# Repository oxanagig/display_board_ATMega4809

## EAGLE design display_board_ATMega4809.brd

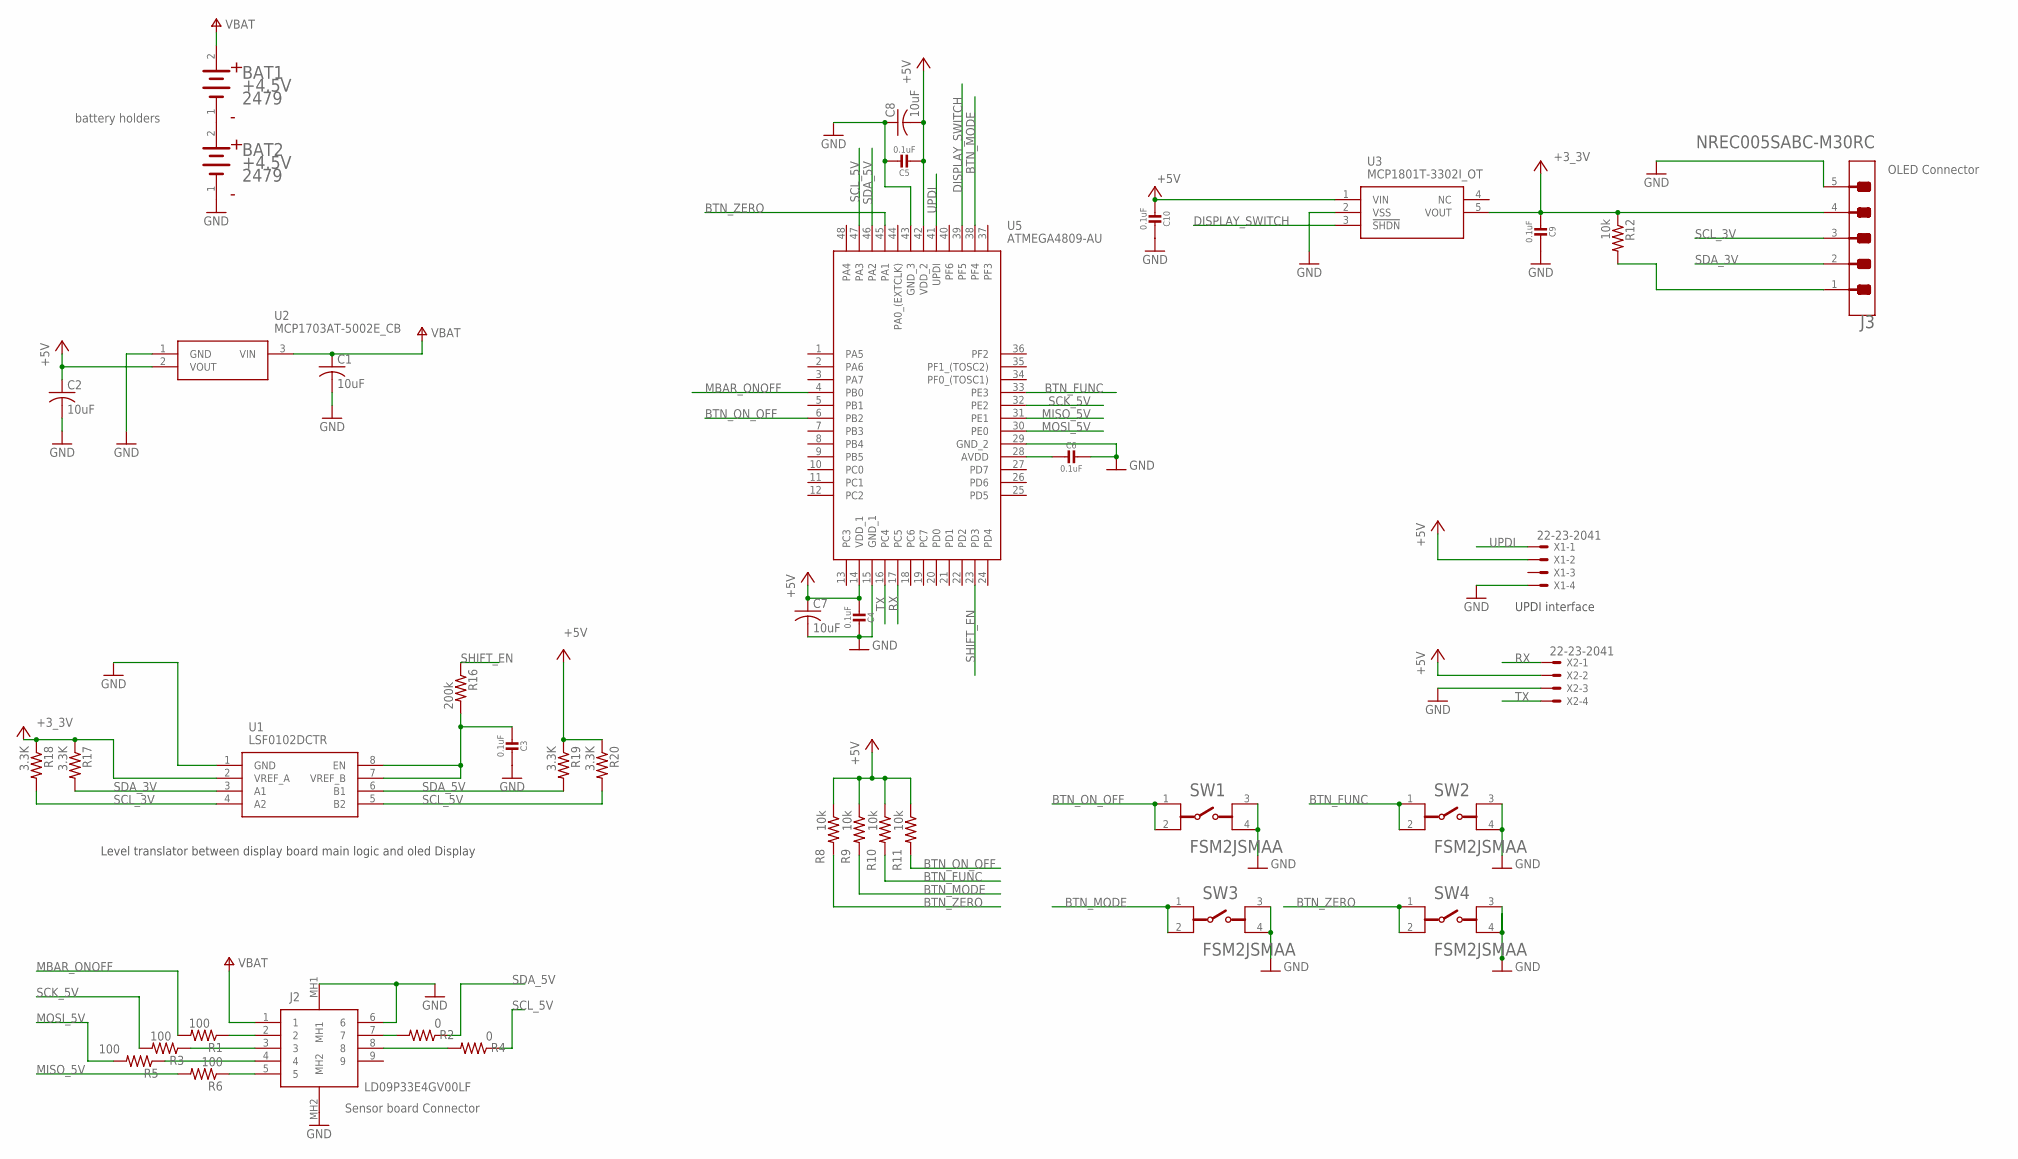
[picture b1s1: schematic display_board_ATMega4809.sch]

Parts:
BAT1, BAT2: KEYSTONE_2479KEYSTONE_2479_0_0; KEYSTONE_2479_0
C1, C2, C7, C8: 10uF; C0805
C3, C4, C5, C6, C9, C10: 0.1uF; _0603MP
J2: LD09P33E4GV00LF
J3: SULLINS_NREC005SABC-M30RCSULLINS_NREC005SABC-M30R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; SULLINS_NREC005SABC-M30RC_0
R1, R3, R5, R6: 100; R0603
R2, R4: 0; R0603
R8, R9, R10, R11, R12: 10k; R0603
R16: 200k; R0603
R17, R18, R19, R20: 3.3K; R0603
SW1, SW2, SW3, SW4: TE_CONNECTIVITY_FSM2JSMAATE_CONNECTIVITY_FSM2JSMA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; TE_CONNECTIVITY_FSM2JSMAA_0
U1: LSF0102DCTR; SOP65P400X130-8N
U2: MCP1703AT-5002E_CB; SOT95P255X145-3N
U3: MCP1801T-3302I_OT; SOT95P270X145-5N
U5: ATMEGA4809-AU; QFP50P900X900X120-48N
X1, X2: 22-23-2041

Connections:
+3V3: C9.2, J3.4, R12.1, R17.1, R18.1, U1.2 (VREF_A), U3.5 (VOUT)
+5V: C2.1, C4.2, C5.2, C7.1, C8.2, C10.2, R8.1, R9.1, R10.1, R11.1, R19.1, R20.1, U2.2 (VOUT), U3.1 (VIN), U5.14 (VDD_1), U5.42 (VDD_2), X1.2, X2.2
BTN_FUNC: R10.2, SW2.1, SW2.2, U5.33 (PE3)
BTN_MODE: R9.2, SW3.1, SW3.2, U5.38 (PF4)
BTN_ON_OFF: R11.2, SW1.1, SW1.2, U5.6 (PB2)
BTN_ZERO: R8.2, SW4.1, SW4.2, U5.45 (PA1)
DISPLAY_RESET: J3.1, R12.2
DISPLAY_SWITCH: U3.3 (!SHDN), U5.39 (PF5)
GND: BAT2.1 (CATHODE), C1.2, C2.2, C3.1, C4.1, C5.1, C6.1, C7.2, C8.1, C9.1, C10.1, J2.6, J2.MH1, J2.MH2, J3.5, SW1.3, SW1.4, SW2.3, SW2.4, SW3.3, SW3.4, SW4.3, SW4.4, U1.1 (GND), U2.1 (GND), U3.2 (VSS), U5.15 (GND_1), U5.29 (GND_2), U5.43 (GND_3), X1.4, X2.3
MBAR_ONOFF: R1.2, U5.4 (PB0)
MISO_5V: R6.2, U5.31 (PE1)
MOSI_5V: R5.2, U5.30 (PE0)
unnamed: C3.2, R16.2, U1.7 (VREF_B), U1.8 (EN)
unnamed: J2.2, R1.1
unnamed: J2.3, R3.1
unnamed: J2.7, R2.2
unnamed: J2.4, R5.1
unnamed: J2.5, R6.1
unnamed: C6.2, U5.28 (AVDD)
unnamed: J2.8, R4.2
unnamed: BAT1.1 (CATHODE), BAT2.2 (ANODE)
RX: U5.17 (PC5), X2.1
SCK_5V: R3.2, U5.32 (PE2)
SCL_3V: J3.3, R18.2, U1.4 (A2)
SCL_5V: R4.1, R20.2, U1.5 (B2), U5.47 (PA3)
SDA_3V: J3.2, R17.2, U1.3 (A1)
SDA_5V: R2.1, R19.2, U1.6 (B1), U5.46 (PA2)
SHIFT_EN: R16.1, U5.23 (PD3)
TX: U5.16 (PC4), X2.4
UPDI: U5.41 (UPDI), X1.1
VBAT: BAT1.2 (ANODE), C1.1, J2.1, U2.3 (VIN)

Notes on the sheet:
OLED Connector
Sensor board Connector
battery holders
UPDI interface
Level translator between display board main logic and oled Display

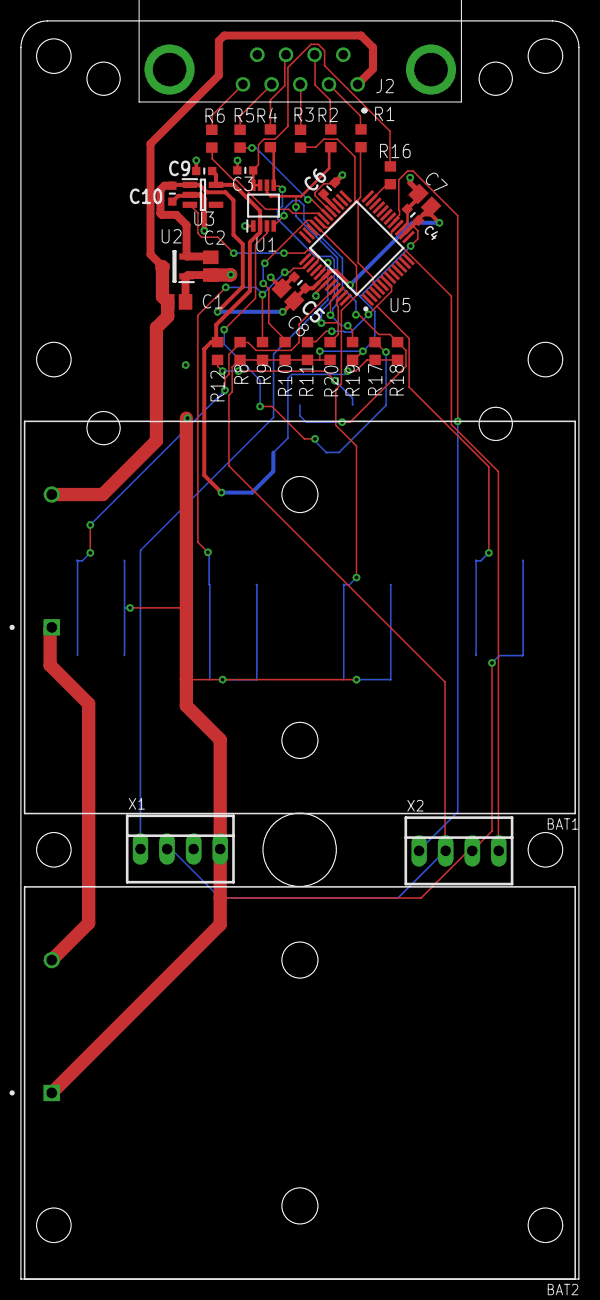
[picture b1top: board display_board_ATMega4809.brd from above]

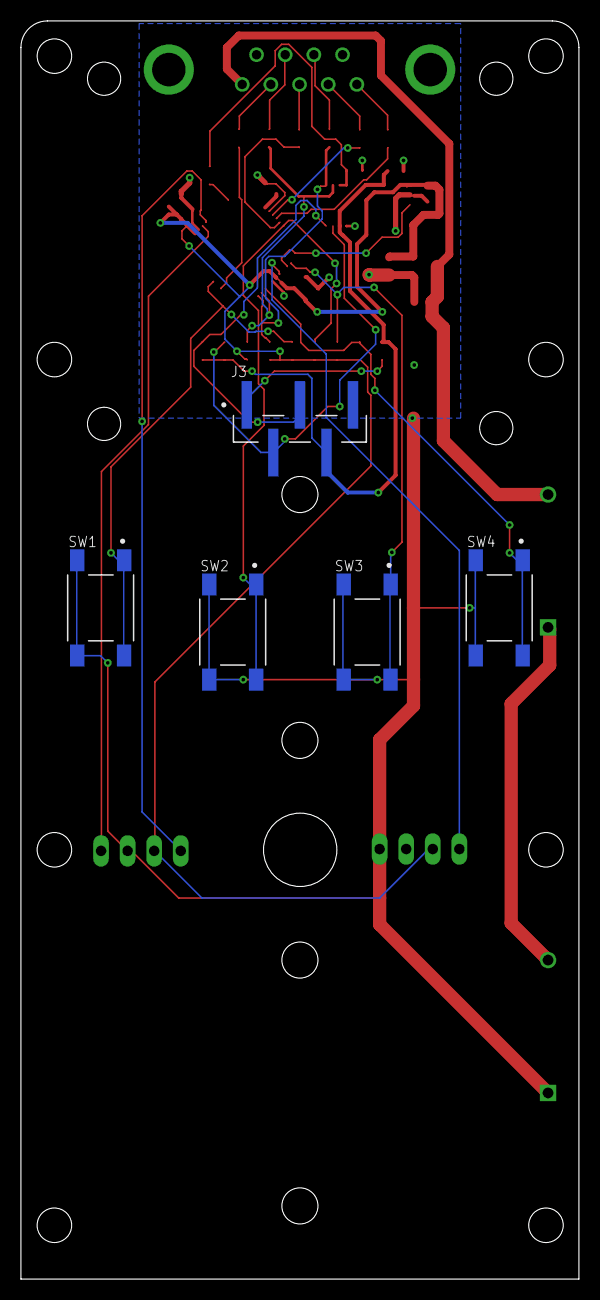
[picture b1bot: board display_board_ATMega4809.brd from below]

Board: 2 copper layers, 53.3 x 120.3 mm, 40 parts (5 on the bottom side), 31 nets.

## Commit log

2022-05-09 Initial commit
    First draft for the schematic
2022-06-05 Added debugging UART connector
2022-06-06 Updated the schematic and initial layout commit
    - Removed the reverse protection PMOS to reduce power consumption(battery holder has mechanical protection already)
    - Initial commit for the layout
2022-06-11 Adding decoupling capacitors
    -Added decoupling capacitors on OLED LDO
    -Added BOM file
2022-07-29 Package update

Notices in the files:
parts and their libraries:
microbuilder: This work is placed in the public domain, and may be freely used for commercial and non-commercial work with the following conditions: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
